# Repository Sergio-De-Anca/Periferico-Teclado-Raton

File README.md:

# Periferico-Teclado-Raton
Este es un trabajo de fin de grado en Ing. Inf. de computadores de la Universidad de Sevilla realizado por Sergio Isidoro De Anca Garabito. 

## Resumen del trabajo
Consiste en la creación de un periférico con funciones de teclado-ratón que puede ser utilizado con una sola mano. 
Para ello se utiliza un microcontrolador que maneja “switches”, “joysticks”, sensor “IMU” y pantalla y envía instrucciones al ordenador.

## Organización del proyecto
- FuncionamientoPrototipo: Se ven una serie de vídeos e imágenes del funcionamiento del prototipo sobre una protoboard
- ImplementacionConjunto: Contiene el firmware del dispositivo
- IntentoDescriptorHID/PerifericoTFG: Subido una librería donde se trata de convertir el mC en un dispositivo HID. 
- PCB_TFG: Contiene el diseño de la primera iteración de la PCB del periférico

Si tiene dudas sobre el proyecto, contactar por email: Sergioanca14@gmail.com

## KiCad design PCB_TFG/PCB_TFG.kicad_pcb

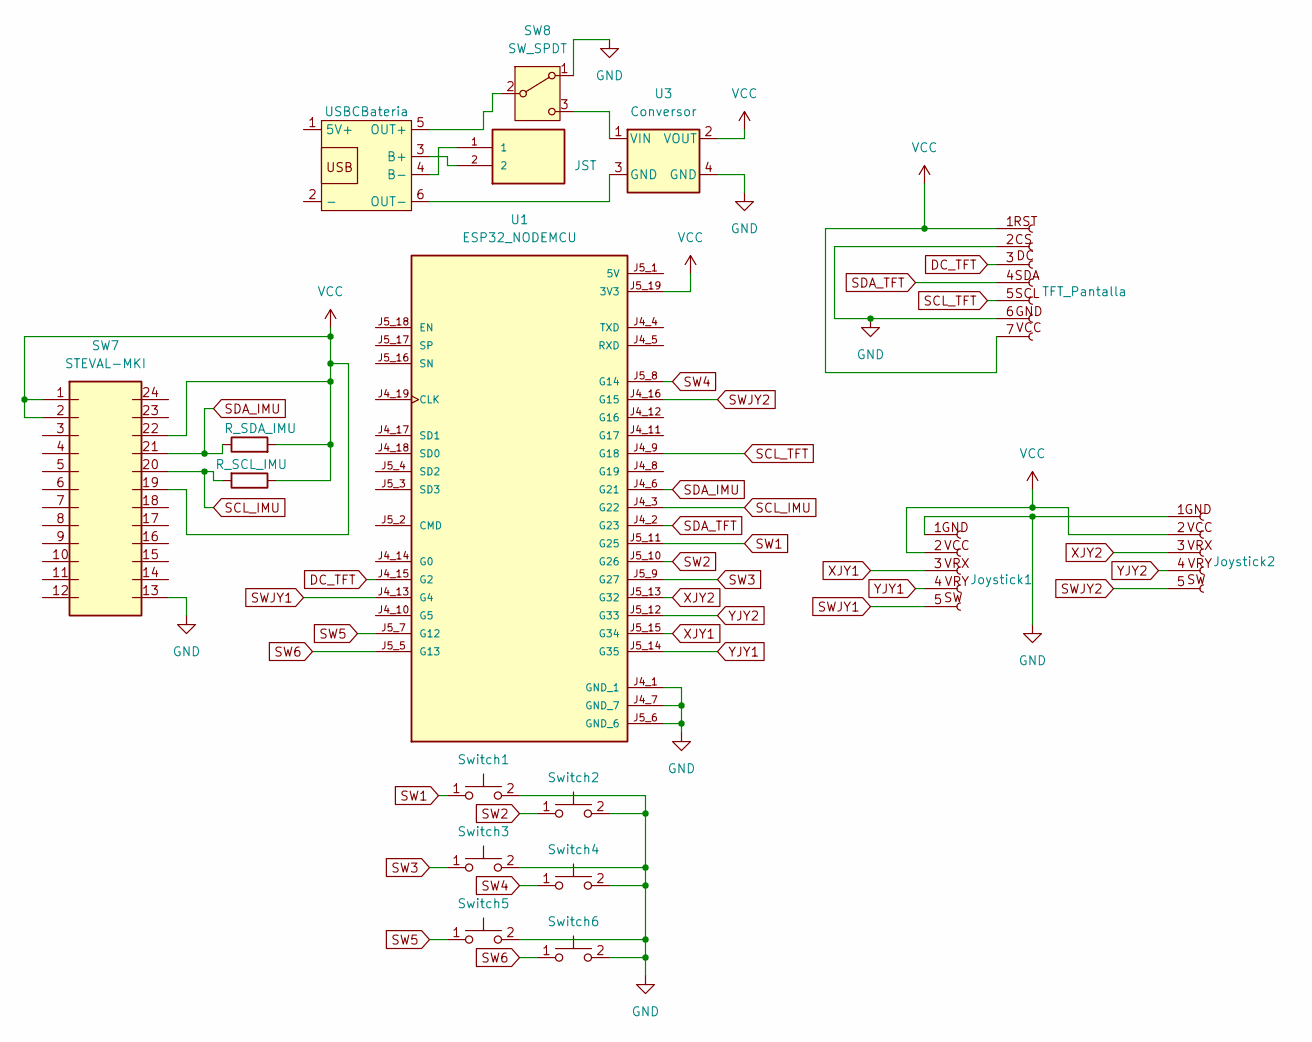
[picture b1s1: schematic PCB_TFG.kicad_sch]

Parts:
J1: JST; JST_S2B-PH-K-S_LF__SN_
J2: TFT_Pantalla; PinSocket_1x07_P2.54mm_Vertical
J3: Joystick1; PinHeader_1x05_P2.54mm_Vertical
J4: Joystick2; PinHeader_1x05_P2.54mm_Vertical
R1: R_SDA_IMU; R_Axial_DIN0204_L3.6mm_D1.6mm_P1.90mm_Vertical
R2: R_SCL_IMU; R_Axial_DIN0204_L3.6mm_D1.6mm_P1.90mm_Vertical
SW1: Switch1; SW_Cherry_MX_1.00u_Plate
SW2: Switch2; SW_Cherry_MX_1.00u_Plate
SW3: Switch3; SW_Cherry_MX_1.00u_Plate
SW4: Switch4; SW_Cherry_MX_1.00u_Plate
SW5: Switch5; SW_Cherry_MX_1.00u_Plate
SW6: Switch6; SW_Cherry_MX_1.00u_Plate
SW7: STEVAL-MKI; STEVAL-MKI229A
SW8: SW_SPDT; SW_Slide-03_Wuerth-WS-SLTV_10x2.5x6.4_P2.54mm
TP1: USBCBateria; TP4056-Module
U1: ESP32_NODEMCU; MODULE_ESP32_NODEMCU
U3: Conversor

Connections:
DC_TFT: J2.3, U1.J4_15 (G2)
GND: J2.2, J2.6, J3.1, J4.1, SW1.2 (D), SW2.2 (D), SW3.2 (D), SW4.2 (D), SW5.2 (D), SW6.2 (D), SW7.13 (GND), SW8.1 (A), U1.J4_1 (GND_1), U1.J4_7 (GND_7), U1.J5_6 (GND_6), U3.4 (GND)
unnamed: SW8.2 (B), TP1.5 (OUT+)
unnamed: SW8.3 (C), U3.1 (VIN)
unnamed: J1.2, TP1.3 (B+)
unnamed: J1.1, TP1.4 (B-)
unnamed: TP1.6 (OUT-), U3.3 (GND)
SCL_IMU: R2.2, SW7.20 (SCL), U1.J4_3 (G22)
SCL_TFT: J2.5, U1.J4_9 (G18)
SDA_IMU: R1.1, SW7.21 (SDA), U1.J4_6 (G21)
SDA_TFT: J2.4, U1.J4_2 (G23)
SW1: SW1.1 (C), U1.J5_11 (G25)
SW2: SW2.1 (C), U1.J5_10 (G26)
SW3: SW3.1 (C), U1.J5_9 (G27)
SW4: SW4.1 (C), U1.J5_8 (G14)
SW5: SW5.1 (C), U1.J5_7 (G12)
SW6: SW6.1 (C), U1.J5_5 (G13)
SWJY1: J3.5, U1.J4_13 (G4)
SWJY2: J4.5, U1.J4_16 (G15)
VCC: J2.1, J2.7, J3.2, J4.2, R1.2, R2.1, SW7.1 (VDD), SW7.2 (VDDIO), SW7.19 (CS), SW7.22 (SDO), U1.J5_19 (3V3), U3.2 (VOUT)
XJY1: J3.3, U1.J5_15 (G34)
XJY2: J4.3, U1.J5_13 (G32)
YJY1: J3.4, U1.J5_14 (G35)
YJY2: J4.4, U1.J5_12 (G33)

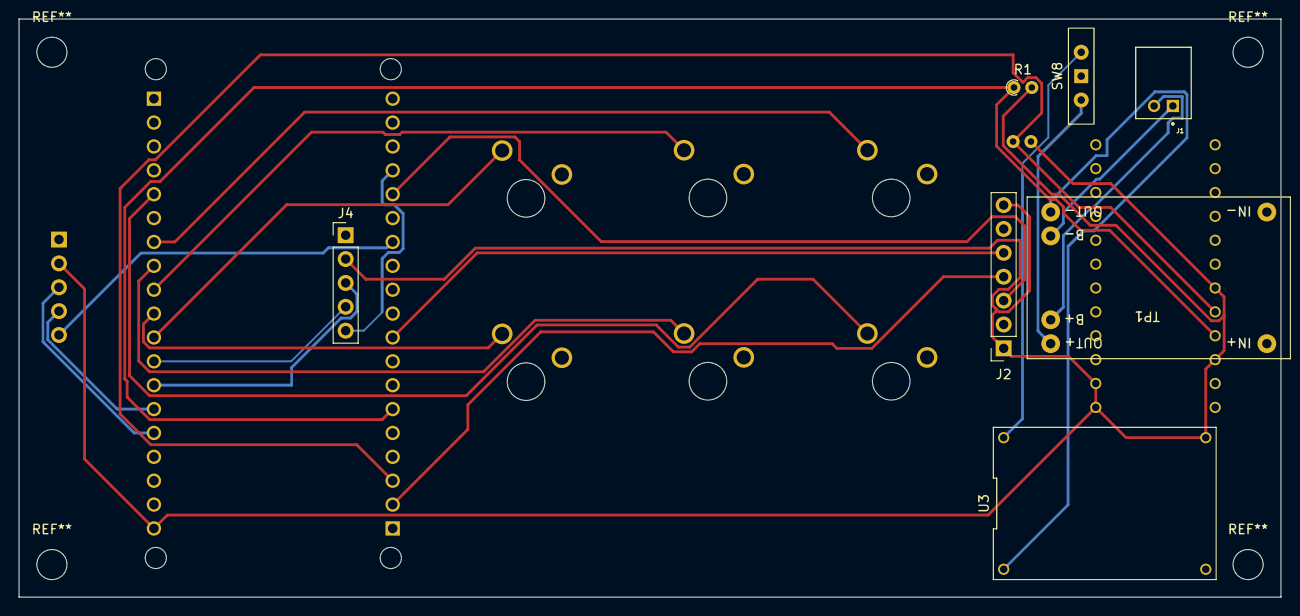
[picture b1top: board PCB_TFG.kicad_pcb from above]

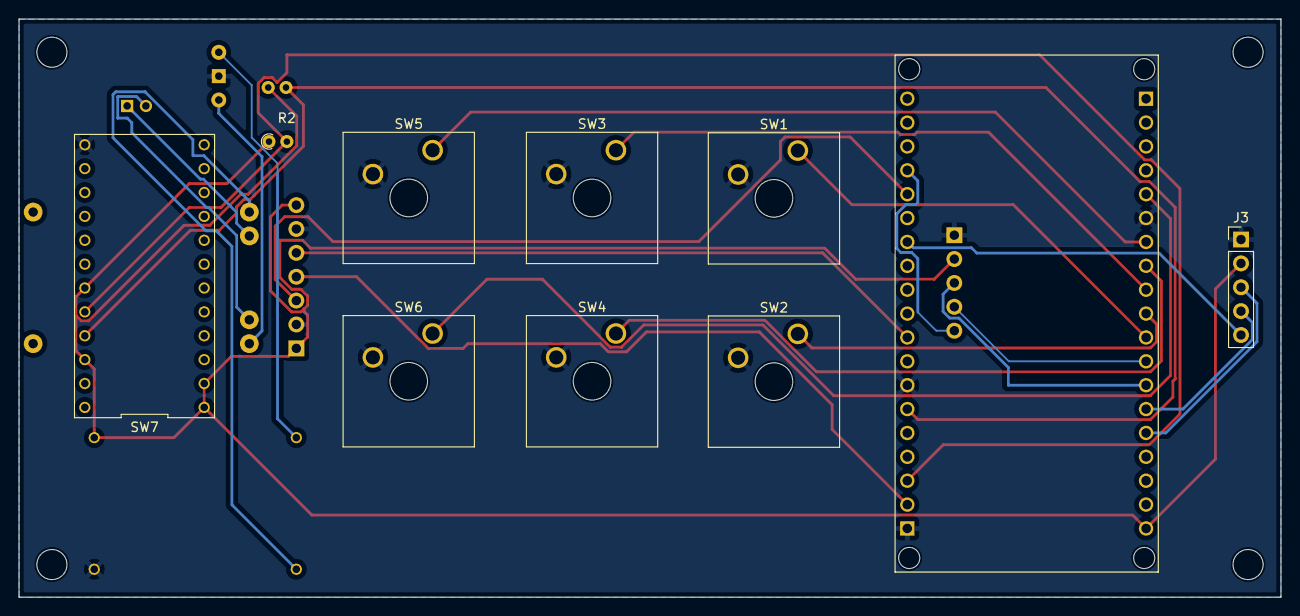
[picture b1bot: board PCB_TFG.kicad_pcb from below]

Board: 2 copper layers, 134.2 x 61.5 mm, 17 parts (10 on the bottom side), 24 nets.

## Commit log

2025-10-01 Añadido Firmware
2025-10-01 Añadido diseño de la PCB
2025-10-01 Añadido descriptor HID
2025-10-06 Añadido Intento del descriptor HID y el funcionamiento del prototipo
2025-11-06 Actualización Interruptor
